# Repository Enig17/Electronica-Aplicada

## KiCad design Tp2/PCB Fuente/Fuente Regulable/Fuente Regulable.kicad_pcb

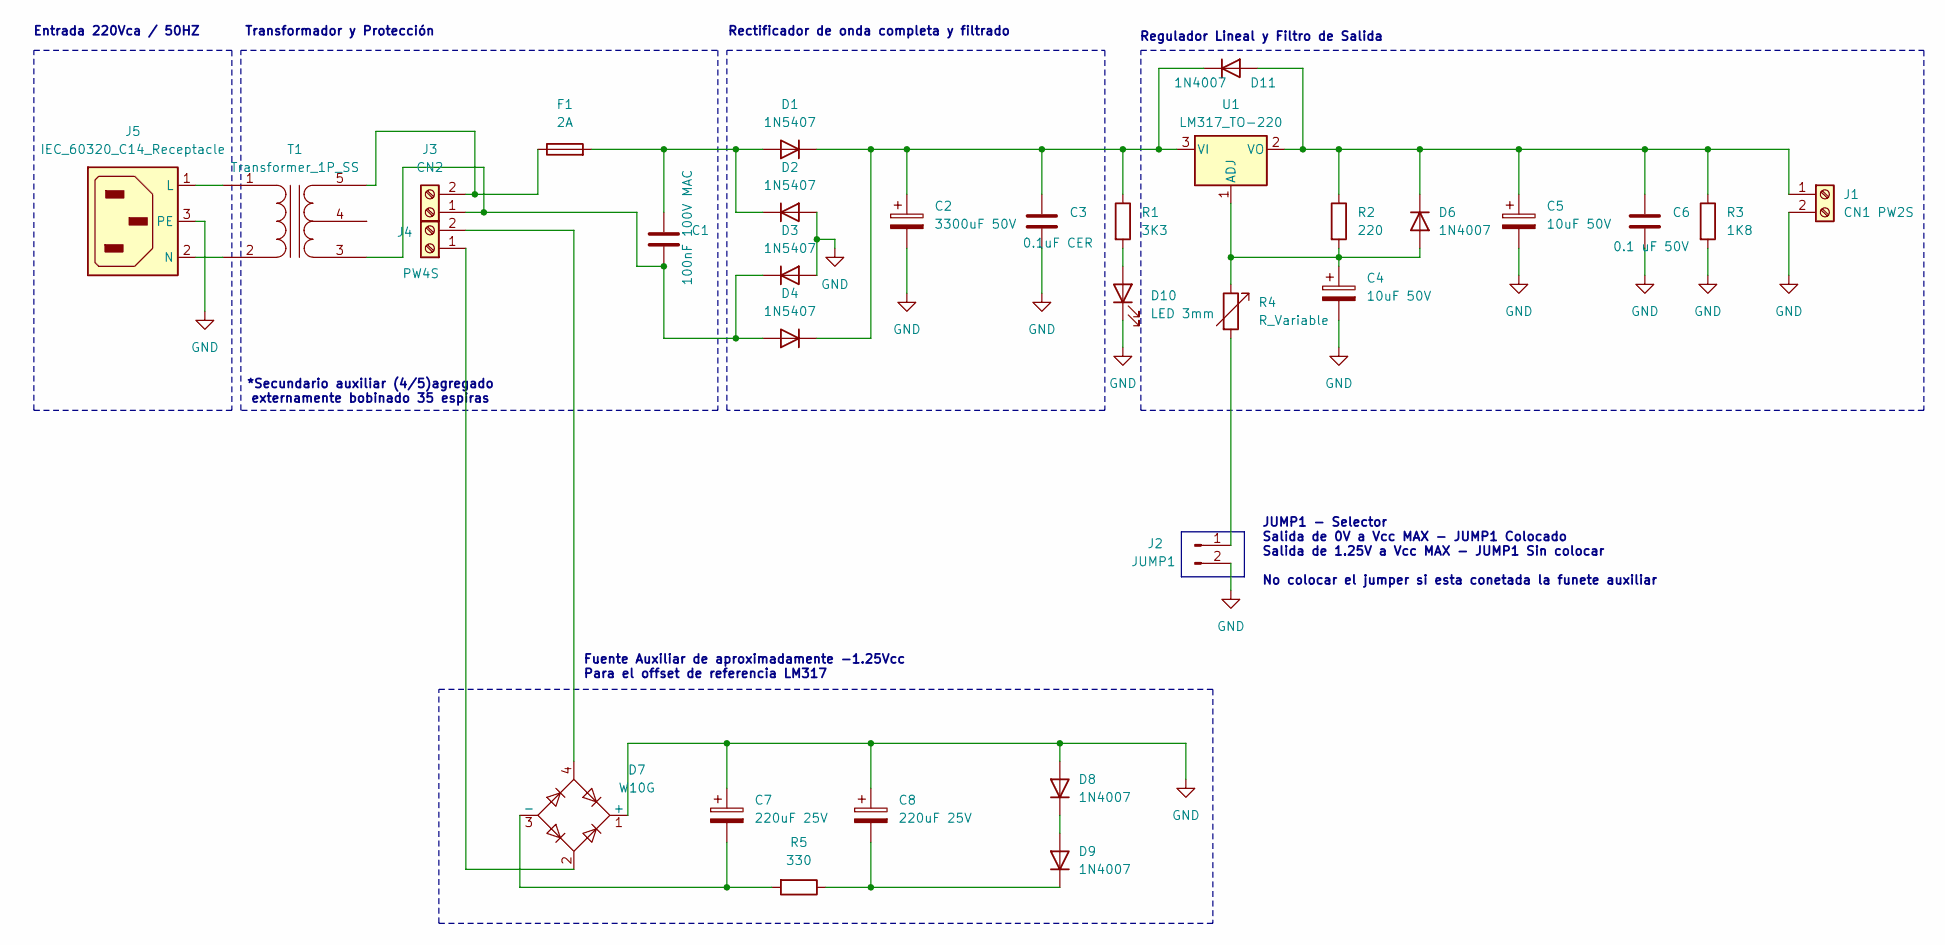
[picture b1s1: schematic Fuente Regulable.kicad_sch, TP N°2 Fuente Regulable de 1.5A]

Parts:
C1: 100nF 100V MAC; C_Rect_L16.5mm_W4.7mm_P15.00mm_MKT
C2: 3300uF 50V; CP_Radial_D18.0mm_P7.50mm
C3: 0.1uF CER; C_Disc_D5.0mm_W2.5mm_P5.00mm
C4, C5: 10uF 50V; CP_Radial_D5.0mm_P2.50mm
C6: 0.1 uF 50V; C_Disc_D5.0mm_W2.5mm_P5.00mm
C7, C8: 220uF 25V; CP_Radial_D5.0mm_P2.50mm
D1, D2, D3, D4: 1N5407; D_DO-201AD_P15.24mm_Horizontal
D6, D8, D9, D11: 1N4007; D_DO-41_SOD81_P10.16mm_Horizontal
D7: W10G; Diode_Bridge_Round_D9.8mm
D10: LED 3mm; LED_D5.0mm
F1: 2A; Fuseholder_Cylinder-5x20mm_Stelvio-Kontek_PTF78_Horizontal_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
J1: CN1 PW2S; TerminalBlock_MaiXu_MX126-5.0-02P_1x02_P5.00mm
J2: JUMP1; PinHeader_2x01_P2.54mm_Vertical
J3: CN2; TerminalBlock_MaiXu_MX126-5.0-02P_1x02_P5.00mm
J4: PW4S; TerminalBlock_MaiXu_MX126-5.0-02P_1x02_P5.00mm
J5: IEC_60320_C14_Receptacle
R1: 3K3; R_Axial_DIN0207_L6.3mm_D2.5mm_P10.16mm_Horizontal
R2: 220; R_Axial_DIN0207_L6.3mm_D2.5mm_P7.62mm_Horizontal
R3: 1K8; R_Axial_DIN0207_L6.3mm_D2.5mm_P7.62mm_Horizontal
R4: R_Variable; TerminalBlock_MaiXu_MX126-5.0-02P_1x02_P5.00mm
R5: 330; R_Axial_DIN0207_L6.3mm_D2.5mm_P7.62mm_Horizontal
T1: Transformer_1P_SS
U1: LM317_TO-220; TerminalBlock_MaiXu_MX126-5.0-03P_1x03_P5.00mm

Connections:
GND: C2.2, C3.2, C4.2, C5.2, C6.2, C7.1, C8.1, D2.2 (A), D3.2 (A), D7.1 (+), D8.2 (A), D10.1 (K), J1.2, J2.2, J5.3 (PE), R3.2
unnamed: C1.1, D1.2 (A), D2.1 (K), F1.2
unnamed: C2.1, C3.1, D1.1 (K), D4.1 (K), D11.1 (K), R1.1, U1.3 (VI)
unnamed: C1.2, D3.1 (K), D4.2 (A), J3.1, T1.3 (SA)
unnamed: C4.1, D6.2 (A), R2.2, R4.1, U1.1 (ADJ)
unnamed: C7.2, D7.3 (-), R5.2
unnamed: D8.1 (K), D9.2 (A)
unnamed: C8.2, D9.1 (K), R5.1
unnamed: D10.2 (A), R1.2
unnamed: C5.1, C6.1, D6.1 (K), D11.2 (A), J1.1, R2.1, R3.1, U1.2 (VO)
unnamed: J2.1, R4.2
unnamed: F1.1, J3.2, T1.5 (SB)
unnamed: D7.2, J4.1
unnamed: D7.4, J4.2
unnamed: J5.1 (L), T1.1 (AA)
unnamed: J5.2 (N), T1.2 (AB)

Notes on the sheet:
Rectificador de onda completa y filtrado
Entrada 220Vca / 50HZ
Fuente Auxiliar de aproximadamente -1.25Vcc Para el offset de referencia LM317
Regulador Lineal y Filtro de Salida
JUMP1 - Selector Salida de 0V a Vcc MAX - JUMP1 Colocado Salida de 1.25V a Vcc MAX - JUMP1 Sin colocar No colocar el jumper si esta conetada la funete auxiliar
Transformador y Protección
*Secundario auxiliar (4/5)agregado externamente bobinado 35 espiras

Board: 2 copper layers, 29 parts (0 on the bottom side), 14 nets, no tracks yet.

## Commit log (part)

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2026-05-21 primer commit
